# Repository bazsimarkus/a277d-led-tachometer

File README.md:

# a277d-led-tachometer

An analog LED tachometer controlled by an East German A277D chip (clone of UAA180), featuring an integrated ATtiny13A-based digital ignition pulse generator for testing.

## Table of Contents

- [Overview](#overview)
- [Features](#features)
- [History](#history)
- [Hardware Description](#hardware-description)
  - [Tachometer Circuit](#tachometer-circuit)
  - [Pulse Generator Circuit](#pulse-generator-circuit)
- [Components (BOM)](#components-bom)
- [How It Works](#how-it-works)
  - [Tachometer Operation](#tachometer-operation)
  - [Pulse Generator Operation](#pulse-generator-operation)
- [Getting Started](#getting-started)
  - [Prerequisites](#prerequisites)
  - [Hardware Assembly](#hardware-assembly)
  - [Programming the ATtiny13A](#programming-the-attiny13a)
  - [Calibration](#calibration)
- [Usage](#usage)
- [Troubleshooting](#troubleshooting)
- [Technical Specifications](#technical-specifications)
- [Acknowledgments](#acknowledgments)

## Overview

This project combines two circuit boards:

1. **Main Tachometer Board**: An analog LED tachometer using the A277D (UAA180 clone) chip that displays engine RPM using a 12-LED bar graph (3 yellow, 6 green, 3 red LEDs)
2. **Digital Pulse Generator Board**: An ATtiny13A-based circuit that generates variable frequency ignition pulses for testing purposes

The pulse generator board is attached to the left side of the main board and can be broken off if the tachometer is to be installed in an actual vehicle.

## Features

- **Analog LED bar graph display** with 12 LEDs (yellow-green-red color scheme)
- **A277D/UAA180 driver chip** for precise LED control
- **Three-point calibration** (sensitivity, scale minimum, scale maximum)
- **Integrated pulse generator** for testing without a vehicle
- **Variable frequency output** (60-200 Hz) with pushbutton control
- **Optocoupled signal isolation** between generator and tachometer
- **12V automotive power supply** with onboard 5V regulation
- **Dual power indicators** (5V and 12V status LEDs)
- **Modular design** - pulse generator can be detached

## History

This circuit has a special history spanning nearly four decades:

In the late 1980s, my father designed this tachometer for his LADA 2105, which lacked a factory-installed tachometer. In 2024, I discovered his original hand-drawn sketches and PCB design prototypes, which inspired me to rebuild this circuit using modern CAD tools while staying true to the original design philosophy.

The base circuit was inspired by a design published on page 213 of the 1987 edition of *Rádiótechnika évkönyve* (Yearbook of Radiotechnics). *Rádiótechnika* was Hungary's longest-running electronics and radio amateur magazine (mid-20th century - 2021), serving as a central resource for hobbyists, engineers, and radio amateurs.

The LED color sequence (yellow-green-red) follows the original design, even though green-yellow-red might be more conventional today.

**Note**: A relevant excerpt from the original 1987 publication is included in `docs/radiotechnika.yearbook.hu1987-203-225.pdf`.

## Hardware Description

### Tachometer Circuit

The main tachometer circuit processes ignition pulses and drives a 12-LED bar graph display.

**Key Components:**
- **IC1 (A277D)**: LED driver chip (East German clone of UAA180)
- **T1 (BC547), T2 (BC557)**: Signal conditioning transistors
- **Z1 (9.1V), Z2 (11V)**: Zener diodes for voltage regulation and protection
- **P1, P2, P3**: 100kΩ trimmer potentiometers for calibration
- **D1-D12**: LED bar graph (3 yellow, 6 green, 3 red)
- **J1, J2**: Terminal blocks for ignition input and 12V power

**Power Requirements:**
- Input: 12-15V DC (automotive)

### Pulse Generator Circuit

The pulse generator uses an ATtiny13A microcontroller to simulate engine ignition pulses.

**Key Components:**
- **U2 (ATtiny13A-P)**: Microcontroller running at 9.6 MHz
- **U1 (PC817)**: Optocoupler for signal isolation and level shifting
- **U3 (L7805)**: 5V voltage regulator for the pulse generator
- **S1**: 12×12mm tactile button (throttle simulation)
- **D13, D15**: Status LEDs (5V and 12V power indicators)
- **J3**: DC-005 power jack
- **J4**: 2-pin female header (pulse output measurement point)
- **J5**: 2-pin male header (connection to tachometer - removable jumper)

**ATtiny13A Pinout:**
```
         ATtiny13A (DIP-8)
         ┌─────┬─┬─────┐
 RESET ──┤1 PB5   VCC 8├── +5V
    NC ──┤2 PB3   PB2 7├── NC (SCK)
BUTTON ──┤3 PB4   PB1 6├── NC (MISO)
   GND ──┤4 GND   PB0 5├── NC (MOSI)
         └─────────────┘
```

**USBasp Programmer Pinout:**
```
    USBasp 10-pin IDC
    ┌─────────────┐
  ──┤1 MOSI  VCC 2├── +5V
  ──┤3 NC    GND 4├── GND
  ──┤5 RESET GND 6├── GND
  ──┤7 SCK   GND 8├── GND
  ──┤9 MISO  GND10├── GND
    └─────────────┘
```

**Programming Connection:**
| USBasp Pin | ATtiny13A Pin | Function |
|------------|---------------|----------|
| VCC (2)    | 8 (VCC)       | +5V      |
| GND (4/6/8/10) | 4 (GND)   | Ground   |
| RESET (5)  | 1 (RESET)     | Reset    |
| SCK (7)    | 7 (PB2)       | Clock    |
| MISO (9)   | 6 (PB1)       | MISO     |
| MOSI (1)   | 5 (PB0)       | MOSI     |

## Components (BOM)

| Item | Qty | Reference(s) | Value | Footprint | Notes |
|------|-----|--------------|-------|-----------|-------|
| 1 | 1 | C1 | 10nF | C_Disc_D3.0mm | Ceramic capacitor |
| 2 | 2 | C2, C7 | 100nF | C_Disc_D7.0mm | Ceramic capacitor |
| 3 | 3 | C3, C5, C6 | 10µF | CP_Radial_D5.0mm | Electrolytic |
| 4 | 1 | C4 | 470µF | CP_Radial_D13.0mm | Electrolytic |
| 5 | 1 | C8 | 0.33µF | C_Disc_D3.0mm | Ceramic capacitor |
| 6 | 1 | C9 | 0.1µF | C_Disc_D3.0mm | Ceramic capacitor |
| 7 | 3 | D1, D2, D3 | LED 5mm YELLOW | LED_D5.0mm | Yellow LEDs |
| 8 | 6 | D4-D9 | LED 5mm GREEN | LED_D5.0mm | Green LEDs |
| 9 | 5 | D10-D13, D15 | LED 5mm RED | LED_D5.0mm | Red LEDs |
| 10 | 1 | D14 | 1N4001 | DO-41 | Rectifier diode |
| 11 | 1 | IC1 | A277D | DIP-18 | LED driver (UAA180 clone) |
| 12 | 2 | J1, J2 | Terminal Block | KF301-2P | 5mm pitch |
| 13 | 1 | J3 | DC-005 | Power Jack | 2.1mm barrel jack |
| 14 | 1 | J4 | Conn_01x02 | PinSocket 2.54mm | Female header |
| 15 | 1 | J5 | Conn_01x02 | PinHeader 2.54mm | Male header |
| 16 | 3 | P1, P2, P3 | 100kΩ | Trimpot RM-065 | Calibration trimmers |
| 17 | 2 | R1, R2 | 4.7kΩ | Axial DIN0207 | 1/4W resistor |
| 18 | 1 | R3 | 47kΩ | Axial DIN0207 | 1/4W resistor |
| 19 | 3 | R4, R5, R8 | 1kΩ | Axial DIN0207 | 1/4W resistor |
| 20 | 1 | R6 | 47Ω | Axial DIN0207 | 1/4W resistor |
| 21 | 1 | R7 | 470Ω | Axial DIN0207 | 1/4W resistor |
| 22 | 1 | R9 | 220Ω | Axial DIN0207 | 1/4W resistor |
| 23 | 1 | R10 | 100kΩ | Axial DIN0207 | 1/4W resistor |
| 24 | 1 | R11 | 2kΩ | Axial DIN0207 | 1/4W resistor |
| 25 | 1 | S1 | Button TACT | 12×12mm | Momentary pushbutton |
| 26 | 1 | T1 | BC547 | TO-92 | NPN transistor |
| 27 | 1 | T2 | BC557 | TO-92 | PNP transistor |
| 28 | 1 | U1 | PC817 | DIP-4 | Optocoupler |
| 29 | 1 | U2 | ATtiny13A-P | DIP-8 | Microcontroller |
| 30 | 1 | U3 | L7805 | TO-220 | 5V voltage regulator |
| 31 | 1 | Z1 | 9.1V Zener | DO-41 | Zener diode |
| 32 | 1 | Z2 | 11V Zener | DO-41 | Zener diode |

**Additional Hardware:**
- DIP-8 socket for U2 (recommended)
- DIP-18 socket for IC1 (recommended)
- Heatsink for U3 (optional, recommended)
- Jumper for J5

## How It Works

### Tachometer Operation

The tachometer circuit operates as follows:

1. **Input Signal Conditioning**: The ignition pulse from J1 or the pulse generator passes through R1, C1, and the transistor pair (T1, T2) for signal conditioning and buffering. Zener diodes Z1 and Z2 provide voltage clamping and protection.

2. **A277D LED Driver**: The conditioned signal feeds into IC1 (A277D), which converts the frequency to an analog voltage and drives the LED bar graph proportionally. The chip includes internal comparators that illuminate LEDs based on the input frequency.

3. **Calibration**:
   - **P1 (Sensitivity)**: Adjusts the overall gain of the circuit
   - **P2 (Scale Min)**: Sets the VREF- reference voltage (minimum scale point)
   - **P3 (Scale Max)**: Sets the VREF+ reference voltage (maximum scale point)

4. **LED Display**: The 12 LEDs illuminate sequentially:
   - D1-D3 (Yellow): Low RPM range (idle to ~2000 RPM)
   - D4-D9 (Green): Normal operating range (~2000-6000 RPM)
   - D10-D12 (Red): High RPM range (>6000 RPM)

The circuit is designed for 4-cylinder engines but can be adapted for other configurations by adjusting the sensitivity trimmer.

### Pulse Generator Operation

The ATtiny13A firmware (`a277d-led-tachometer.ino`) generates a variable-frequency square wave:

1. **Frequency Generation**: A square wave is output on PB3 (pin 2) with adjustable frequency between 60-200 Hz, simulating engine speeds from idle to high RPM.

2. **User Control**: Button S1 on PB4 (pin 3) acts as a "throttle":
   - **Pressed**: Frequency increases at 200 Hz/second
   - **Released**: Frequency decreases at 200 Hz/second

3. **Precise Timing**: The firmware uses `micros()` for accurate frequency generation and smooth frequency transitions.

4. **Signal Isolation**: The square wave passes through optocoupler U1 (PC817), providing:
   - Electrical isolation between 5V logic and 12V tachometer circuits
   - Level shifting to match the tachometer input requirements

5. **Output Points**:
   - **J4**: Measurement point for the optocoupler output
   - **J5**: Connection to the tachometer circuit (removable jumper for external signal testing)

**Firmware Parameters:**
```c
#define MIN_FREQ 60              // Idle frequency (Hz)
#define MAX_FREQ 200             // Maximum frequency (Hz)
#define FREQ_CHANGE_SPEED 200    // Transition rate (Hz/s)
```

## Getting Started

### Prerequisites

**Hardware:**
- Soldering iron and solder
- Multimeter
- USBasp programmer (or compatible AVR ISP)
- 12V DC power supply (1A minimum)
- Breadboard (for initial ATtiny13A programming)
- Jumper wires

**Software:**
- [Arduino IDE 2.3.6](https://www.arduino.cc/en/software) or later
- [MCUdude MicroCore 2.5.1](https://github.com/MCUdude/MicroCore) - ATtiny13 Arduino core

### Hardware Assembly

1. **Solder components** following the schematic and PCB layout:
   - Start with low-profile components (resistors, diodes, IC sockets)
   - Add capacitors and transistors
   - Install connectors and LEDs last
   - Use IC sockets for IC1 and U2 (recommended)

2. **Inspect for shorts** and cold solder joints before applying power

3. **Test voltages**:
   - Apply 12V to J3 or J2
   - Verify 12V at test points
   - Verify 5V at U2 pin 8 (after U3 regulator)

### Programming the ATtiny13A

#### 1. Install USBasp Drivers (Windows)

If the USBasp is not recognized:

1. Download and run [Zadig](https://zadig.akeo.ie/)
2. Select your USBasp device from the list
3. Choose "libusbK" or "libusb-win32" driver
4. Click "Replace Driver"

#### 2. Install MicroCore Board Support

1. Open Arduino IDE
2. Go to **File → Preferences**
3. Add to "Additional Boards Manager URLs":
   ```
   https://mcudude.github.io/MicroCore/package_MCUdude_MicroCore_index.json
   ```
4. Go to **Tools → Board → Boards Manager**
5. Search for "MicroCore" and install version 2.5.1

#### 3. Configure Board Settings

Go to **Tools** menu and select:
- **Board**: "ATtiny13"
- **BOD**: "BOD 2.7V"
- **Clock**: "9.6 MHz internal osc."
- **EEPROM**: "EEPROM retained"
- **Programmer**: "USBasp slow (MicroCore)"

#### 4. Wire the Programmer

Connect the ATtiny13A on a breadboard to the USBasp following the pinout diagram above. Ensure the chip is powered with 5V.

#### 5. Set Fuses and Upload

1. Open `a277d-led-tachometer.ino` in Arduino IDE
2. Click **Tools → Burn Bootloader** (this sets the fuses correctly)
3. Click **Sketch → Upload Using Programmer**

**Expected Output:**
```
Sketch uses 672 bytes (65%) of program storage space. Maximum is 1024 bytes.
Global variables use 18 bytes (28%) of dynamic memory, leaving 46 bytes for local variables.
```

#### 6. Test the Programmed Chip

1. Remove the ATtiny13A from the breadboard
2. Install it in the U2 socket on the PCB
3. Power the circuit with 12V (using the J3 input power jack)
4. Press S1 - the frequency should increase (visible on LEDs)
5. Release S1 - the frequency should decrease

### Calibration

The tachometer requires calibration for accurate RPM display:

#### Method 1: Using the Built-in Pulse Generator

1. Install jumper on J5 (connects pulse generator to tachometer)
2. Apply 12V power
3. Adjust **P1 (Sensitivity)** so that at idle (button released), 1-2 yellow LEDs illuminate
4. Press and hold S1 (maximum frequency)
5. Adjust **P3 (Scale Max)** so that all LEDs illuminate at maximum frequency
6. Adjust **P2 (Scale Min)** to fine-tune the idle position

#### Method 2: Using an External Signal Generator

1. Remove jumper from J5
2. Connect a function generator to J1:
   - Frequency: 60 Hz (idle) to 200 Hz (max)
   - Amplitude: 5-12V pulses
3. Apply 12V power to J2/J3
4. At 60 Hz, adjust **P1** for 1-2 yellow LEDs
5. At 200 Hz, adjust **P3** for all LEDs illuminated
6. Fine-tune with **P2**

#### Method 3: In-Vehicle Calibration

1. **Remove** the pulse generator board (break at perforation)
2. Connect J1 to the vehicle's ignition coil negative terminal
3. Connect J2 to vehicle 12V (fused, ignition-switched preferred)
4. Start engine and let it idle
5. Adjust **P1** for 1-2 yellow LEDs at idle
6. Rev engine to redline (carefully!)
7. Adjust **P3** so all LEDs illuminate near redline
8. Fine-tune **P2** for desired idle indication

**Note**: For engines other than 4-cylinder, you may need to adjust component values (R3, C1) or use an external frequency divider.

## Usage

### Standalone Testing Mode

With the pulse generator attached:

1. Power the circuit with 12V
2. Observe LEDs illuminate at idle frequency
3. Press and hold S1 to simulate acceleration
4. Release S1 to return to idle
5. Status LEDs D13 (5V) and D15 (12V) confirm proper power supply

### External Signal Mode

1. Remove jumper from J5
2. Connect your signal source to J1
3. Monitor the optocoupler output at J4 if needed
4. The tachometer responds to 5-12V pulses at 30-200 Hz (typical engine range)

### Vehicle Installation Mode

1. Carefully break off the pulse generator section at the PCB perforation
2. Mount the tachometer board in the vehicle dashboard
3. Connect:
   - J2 (+12V) to fused ignition-switched 12V
   - J2 (GND) to vehicle chassis ground
   - J1 (IGNITION) to ignition coil negative terminal
   - J1 (GND) to chassis ground
4. Calibrate as described above

## Troubleshooting

| Problem | Possible Cause | Solution |
|---------|----------------|----------|
| No LEDs illuminate | No power | Check 12V supply, fuse, polarity |
| No 5V at U2 pin 8 | U3 failure or incorrect wiring | Check U3, C5, C6, D14 |
| Status LEDs don't light | LED polarity reversed | Check D13, D15 orientation |
| Pulse generator doesn't work | ATtiny13A not programmed | Reprogram with correct fuses |
| Button does nothing | Wrong pin or bad solder joint | Check S1, R8, U2 pin 3 connection |
| No LED response to pulses | Signal not reaching IC1 | Check J5 jumper, U1, T1, T2, capacitors |
| LEDs always full or empty | Calibration issue | Adjust P1, P2, P3 trimmers |
| Erratic LED behavior | Noisy input signal | Add capacitance at J1, check grounding |
| USBasp not recognized | Driver issue (Windows) | Install drivers with Zadig |
| Upload fails | Wrong programmer settings | Select "USBasp slow" or use "-B32" flag |

**Common Arduino IDE Errors:**

- **"avrdude: error: cannot set sck period"**: This is a harmless warning with older USBasp firmware. The upload should still succeed.
- **"Device signature not found"**: Check wiring, ensure 5V power to ATtiny13A, try slower clock with "-B32".

## Technical Specifications

**Tachometer:**
- **Input voltage**: 12V DC nominal (10-15V range)
- **Input signal**: 5-12V ignition pulses, negative-going preferred
- **Frequency range**: ~30-200 Hz (typical 4-cylinder automotive range)
- **LED segments**: 12 (3 yellow, 6 green, 3 red)
- **Calibration range**: Adjustable via three trimpots
- **Power consumption**: ~100 mA at 12V (all LEDs on)

**Pulse Generator:**
- **MCU**: ATtiny13A @ 9.6 MHz internal oscillator
- **Output frequency**: 60-200 Hz (adjustable)
- **Frequency transition**: 200 Hz/second
- **Output**: Optically isolated, 12V pulses
- **Power consumption**: ~40 mA at 5V
- **Firmware size**: 672 bytes (65% of flash)

**PCB:**
- **Dimensions**: 140×60mm combined - main board: 100×60mm, pulse generator: 40×60mm
- **Layers**: 2-layer through-hole design
- **Mounting**: Corner mounting holes on both sub-boards

## Acknowledgments

- **My father, Sandor Markus**: For the original design and inspiration
- **Rádiótechnika magazine**: For publishing the foundational circuit design in 1987
- **MCUdude**: For the excellent [MicroCore](https://github.com/MCUdude/MicroCore) Arduino core
- **The open-source community**: For tools like KiCad, Arduino IDE, and AVRDUDE

---

**Questions or issues?** Open an issue on GitHub or feel free to write me!

**Want to build one?** Share your build photos and experiences - I'd love to see them!

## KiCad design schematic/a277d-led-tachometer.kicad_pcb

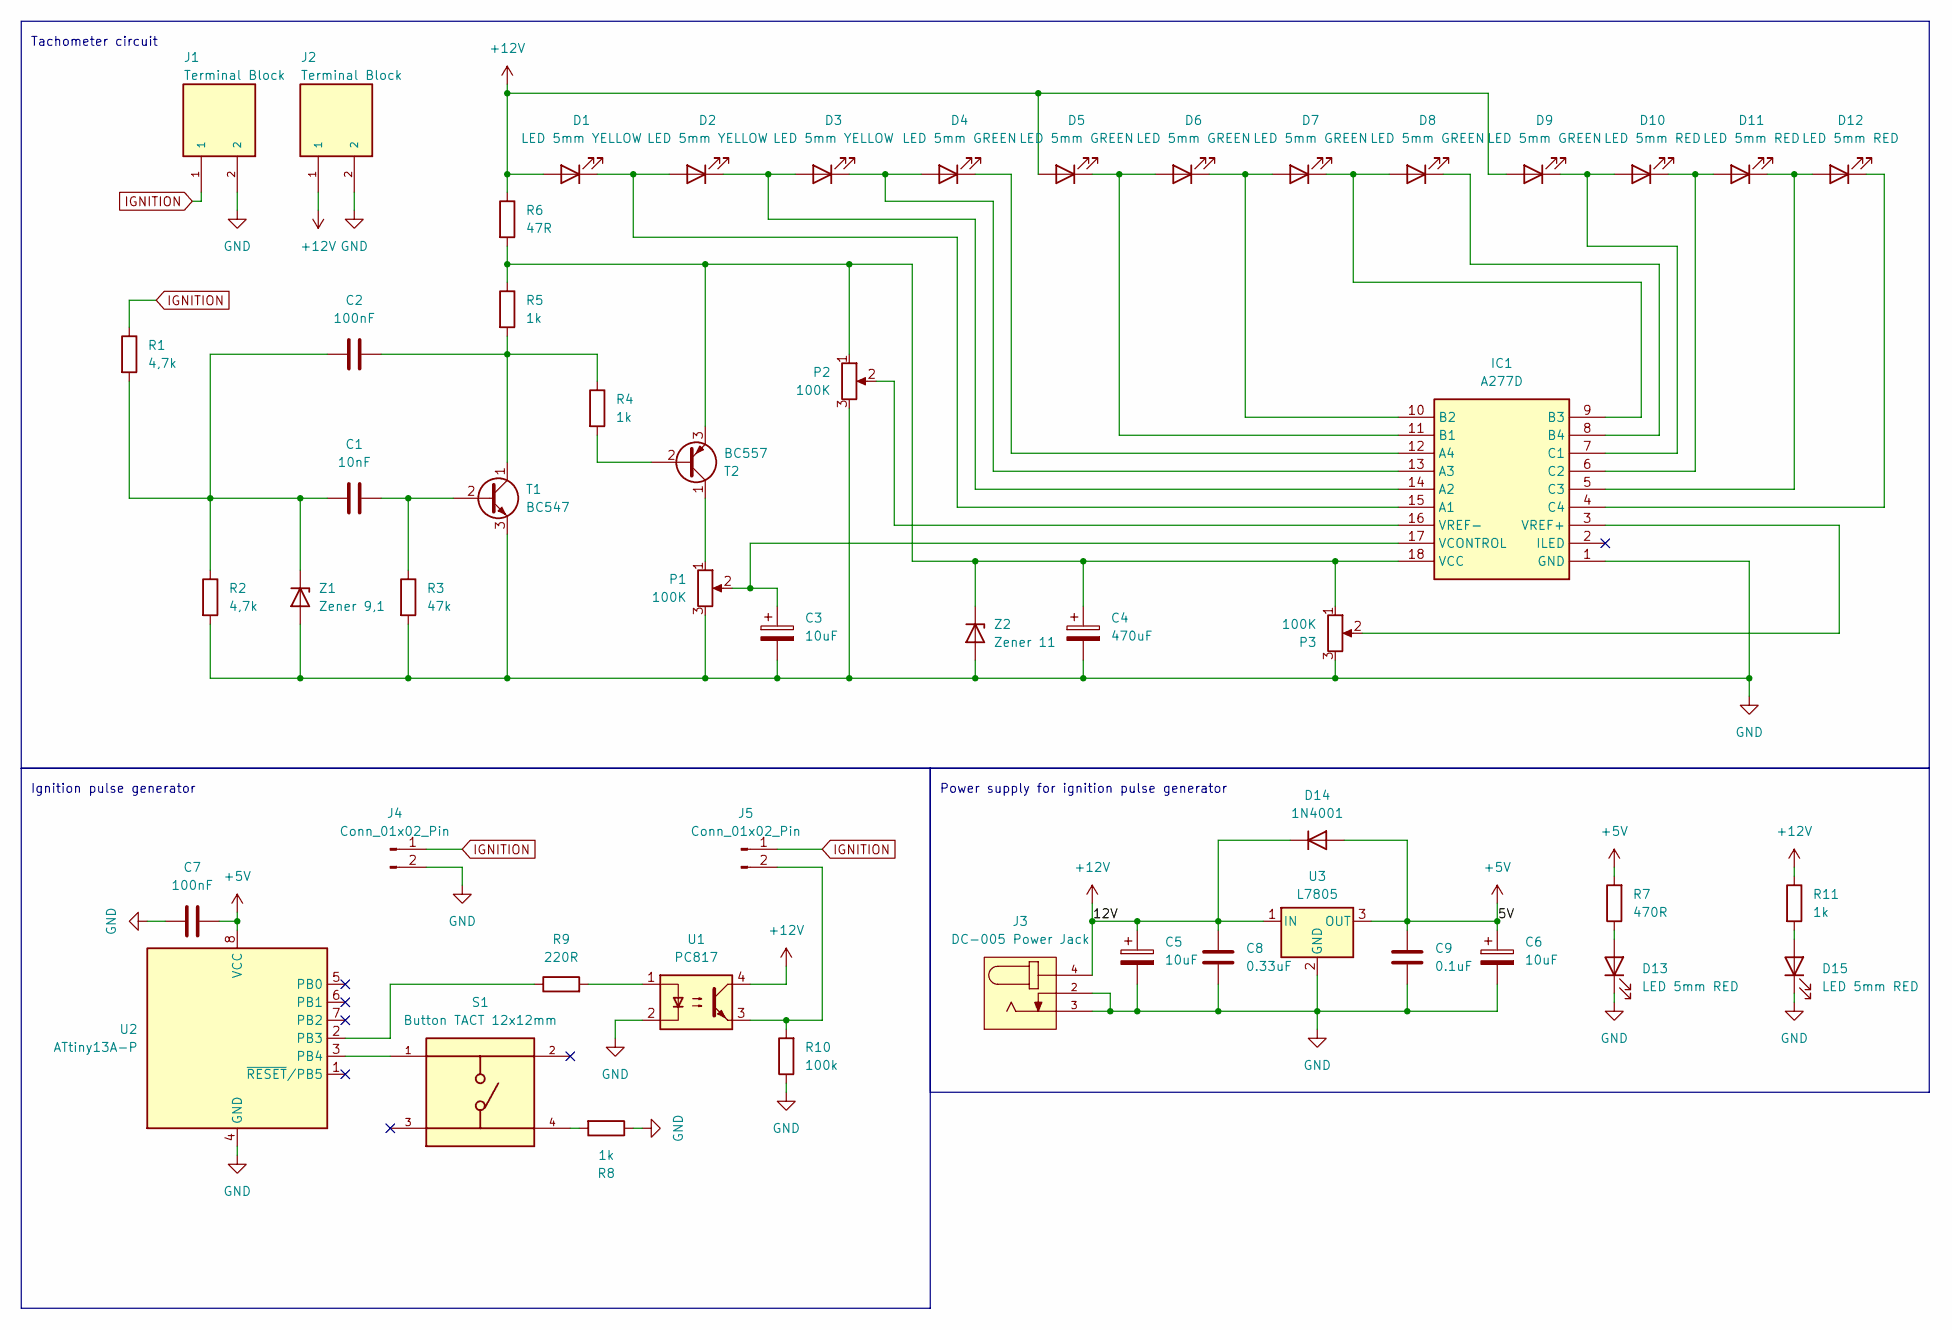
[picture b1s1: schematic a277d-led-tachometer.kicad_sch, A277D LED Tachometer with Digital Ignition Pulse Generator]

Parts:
C1: 10nF; C_Disc_D3.0mm_W1.6mm_P2.50mm
C2, C7: 100nF; C_100nF_L7.0mm_W2.5mm_P5.00mm
C3, C5, C6: 10uF; CP_Radial_D5.0mm_P2.00mm
C4: 470uF; CP_Radial_D13.0mm_P5.00mm
C8: 0.33uF; C_Disc_D3.0mm_W1.6mm_P2.50mm
C9: 0.1uF; C_Disc_D3.0mm_W1.6mm_P2.50mm
D1, D2, D3: LED 5mm YELLOW; LED_D5.0mm_YELLOW
D4, D5, D6, D7, D8, D9: LED 5mm GREEN; LED_D5.0mm_GREEN
D10, D11, D12, D13, D15: LED 5mm RED; LED_D5.0mm_RED
D14: 1N4001; D_DO-41_SOD81_P10.16mm_Horizontal
IC1: A277D; DIP-18_W7.62mm_Socket
J1, J2: Terminal Block; Terminal Block KF301-2P; PARTREV NA
J3: DC-005 Power Jack
J4: Conn_01x02_Pin; PinSocket_1x02_P2.54mm_Vertical
J5: Conn_01x02_Pin; PinHeader_1x02_P2.54mm_Vertical
P1, P2, P3: 100K; Trimpot RM-065
R1, R2: 4,7k; R_Axial_DIN0207_L6.3mm_D2.5mm_P10.16mm_Horizontal
R3: 47k; R_Axial_DIN0207_L6.3mm_D2.5mm_P10.16mm_Horizontal
R4, R5, R8, R11: 1k; R_1k_Axial_DIN0207
R6: 47R; R_Axial_DIN0207_L6.3mm_D2.5mm_P10.16mm_Horizontal
R7: 470R; R_470_Axial_DIN0207
R9: 220R; R_Axial_DIN0207_L6.3mm_D2.5mm_P10.16mm_Horizontal
R10: 100k; R_Axial_DIN0207_L6.3mm_D2.5mm_P10.16mm_Horizontal
S1: Button TACT 12x12mm; PARTREV 1.0
T1: BC547; TO-92_Inline
T2: BC557; TO-92_Inline
U1: PC817; DIP-4_W7.62mm
U2: ATtiny13A-P; DIP-8_W7.62mm
U3: L7805; TO-220-3_Vertical
Z1: Zener 9,1; D_DO-41_SOD81_P10.16mm_Horizontal
Z2: Zener 11; D_DO-41_SOD81_P10.16mm_Horizontal

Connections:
+5V: C6.1, C7.2, C9.2, D14.2 (A), R7.2, U2.8 (VCC), U3.3 (OUT)
+12V: C5.1, C8.2, D1.2 (A), D5.2 (A), D9.2 (A), D14.1 (K), J2.1, J3.4, R6.1, R11.1, U1.4, U3.1 (IN)
GND: C3.2, C4.2, C5.2, C6.2, C7.1, C8.1, C9.1, D13.1 (K), D15.1 (K), IC1.1 (GND), J1.2, J2.2, J3.2, J3.3, J4.2, P1.3, P2.3, P3.3, R2.2, R3.2, R8.1, R10.1, T1.3 (E), U1.2, U2.4 (GND), U3.2 (GND), Z1.2 (A), Z2.2 (A)
IGNITION: J1.1, J4.1, J5.1, R1.1
unnamed: D1.1 (K), D2.2 (A), IC1.15 (A1)
unnamed: D2.1 (K), D3.2 (A), IC1.14 (A2)
unnamed: D3.1 (K), D4.2 (A), IC1.13 (A3)
unnamed: D4.1 (K), IC1.12 (A4)
unnamed: D5.1 (K), D6.2 (A), IC1.11 (B1)
unnamed: D6.1 (K), D7.2 (A), IC1.10 (B2)
unnamed: D7.1 (K), D8.2 (A), IC1.9 (B3)
unnamed: D8.1 (K), IC1.8 (B4)
unnamed: D9.1 (K), D10.2 (A), IC1.7 (C1)
unnamed: D10.1 (K), D11.2 (A), IC1.6 (C2)
unnamed: D11.1 (K), D12.2 (A), IC1.5 (C3)
unnamed: D12.1 (K), IC1.4 (C4)
unnamed: D13.2 (A), R7.1
unnamed: D15.2 (A), R11.2
unnamed: C4.1, IC1.18 (VCC), P2.1, P3.1, R5.1, R6.2, T2.3 (E), Z2.1 (K)
unnamed: C3.1, IC1.17 (VCONTROL), P1.2
unnamed: IC1.3 (VREF+), P3.2
unnamed: IC1.16 (VREF-), P2.2
unnamed: J5.2, R10.2, U1.3
unnamed: R8.2, S1.4
unnamed: R9.2, U1.1
unnamed: C1.2, R3.1, T1.2 (B)
unnamed: C2.2, R4.1, R5.2, T1.1 (C)
unnamed: R4.2, T2.2 (B)
unnamed: P1.1, T2.1 (C)
unnamed: R9.1, U2.2 (PB3)
unnamed: S1.1, U2.3 (PB4)
unnamed: C1.1, C2.1, R1.2, R2.1, Z1.1 (K)

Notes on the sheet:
Ignition pulse generator
Tachometer circuit
Power supply for ignition pulse generator

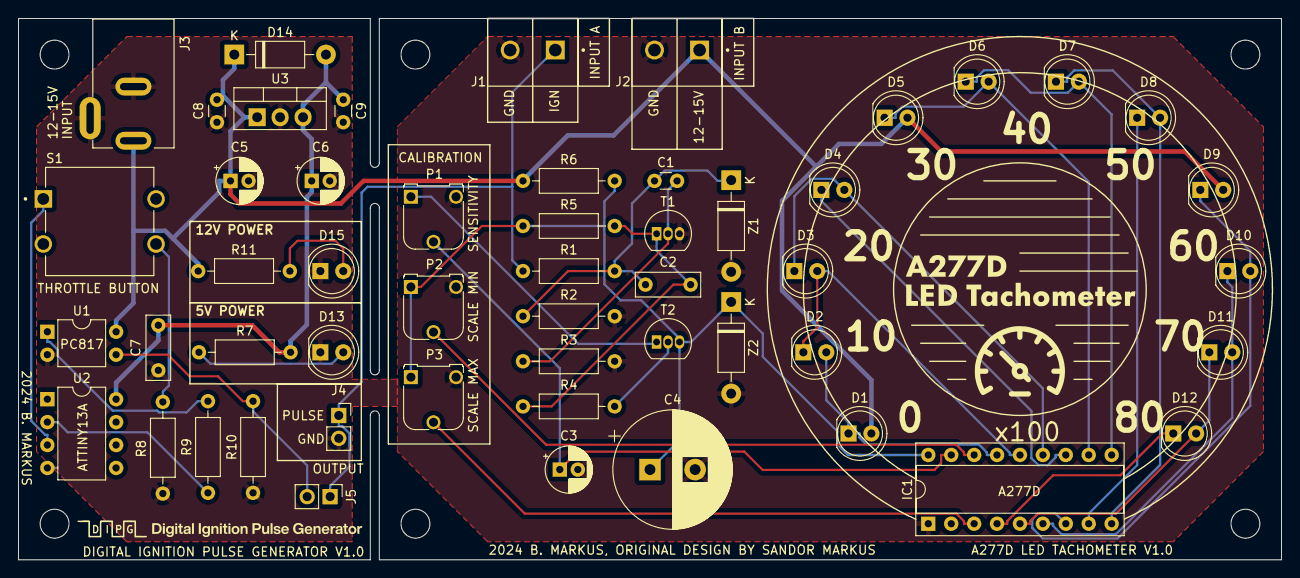
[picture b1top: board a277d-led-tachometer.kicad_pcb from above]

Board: 2 copper layers, 140.0 x 60.0 mm, 60 parts (0 on the bottom side), 32 nets.

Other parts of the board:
G1, G2: LOGO
REF1, REF2, REF3, REF4, REF5, REF6: MountingHole_3.2mm_M3

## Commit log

2024-06-11 Schematic files added
2024-06-25 Footprints updated
2024-06-25 Gerber files added
2024-06-25 PDF schematic added
2024-07-02 12V Power LED resistor updated on schematic
2024-07-02 ATtiny13A ignition pulse generator source code added (Arduino microcore)
2025-10-20 Main PCB board photo added
2025-11-17 Schematic image and second main PCB board photo added
2025-11-17 Original circuit base PDF from 1987 added to docs
2026-02-21 Unnecessary schematic files deleted
2026-02-21 gitignore added to schematic folder
